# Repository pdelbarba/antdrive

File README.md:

# Antdrive
Magnettic loop antenna driver arduino shield for amateur radio HF

## Notes
Only one limit switch is pinned out as my setup limits torque such that the capacitor cannot be damaged on the other end. If using standard ethernet cable, you have another two lines (one twisted pair) that can be used for additional switches and signaling however.  I may add this at some point but I'm currently focused on other projects.

## Parts

Designed for the Pololu #1208 stepper motor (https://www.pololu.com/product/1208).  While only rated for 10V it has no issues running at >15v for tuning as the Arduino sketch keeps the motor powered off when not rotating to minimize EMI.  The mounting hardware I used is also available from Pololu.

The motor driver module is an A4988 based board also from Pololu (https://www.pololu.com/product/1182).  In theory it should be able to handle much larger stepper motors, 2A per phase and 35V.

Misc drive hardware is as follows:

https://www.amazon.com/gp/product/B07RXJ5GVG/  Drive side pulley

https://www.amazon.com/gp/product/B07W5L6G8L/  Capacitor side pulley

https://www.amazon.com/gp/product/B07KK86NYX/  Note: I've found these belts to be free of metalic strapping which is important for preventing arcing between the capacitor and the motor

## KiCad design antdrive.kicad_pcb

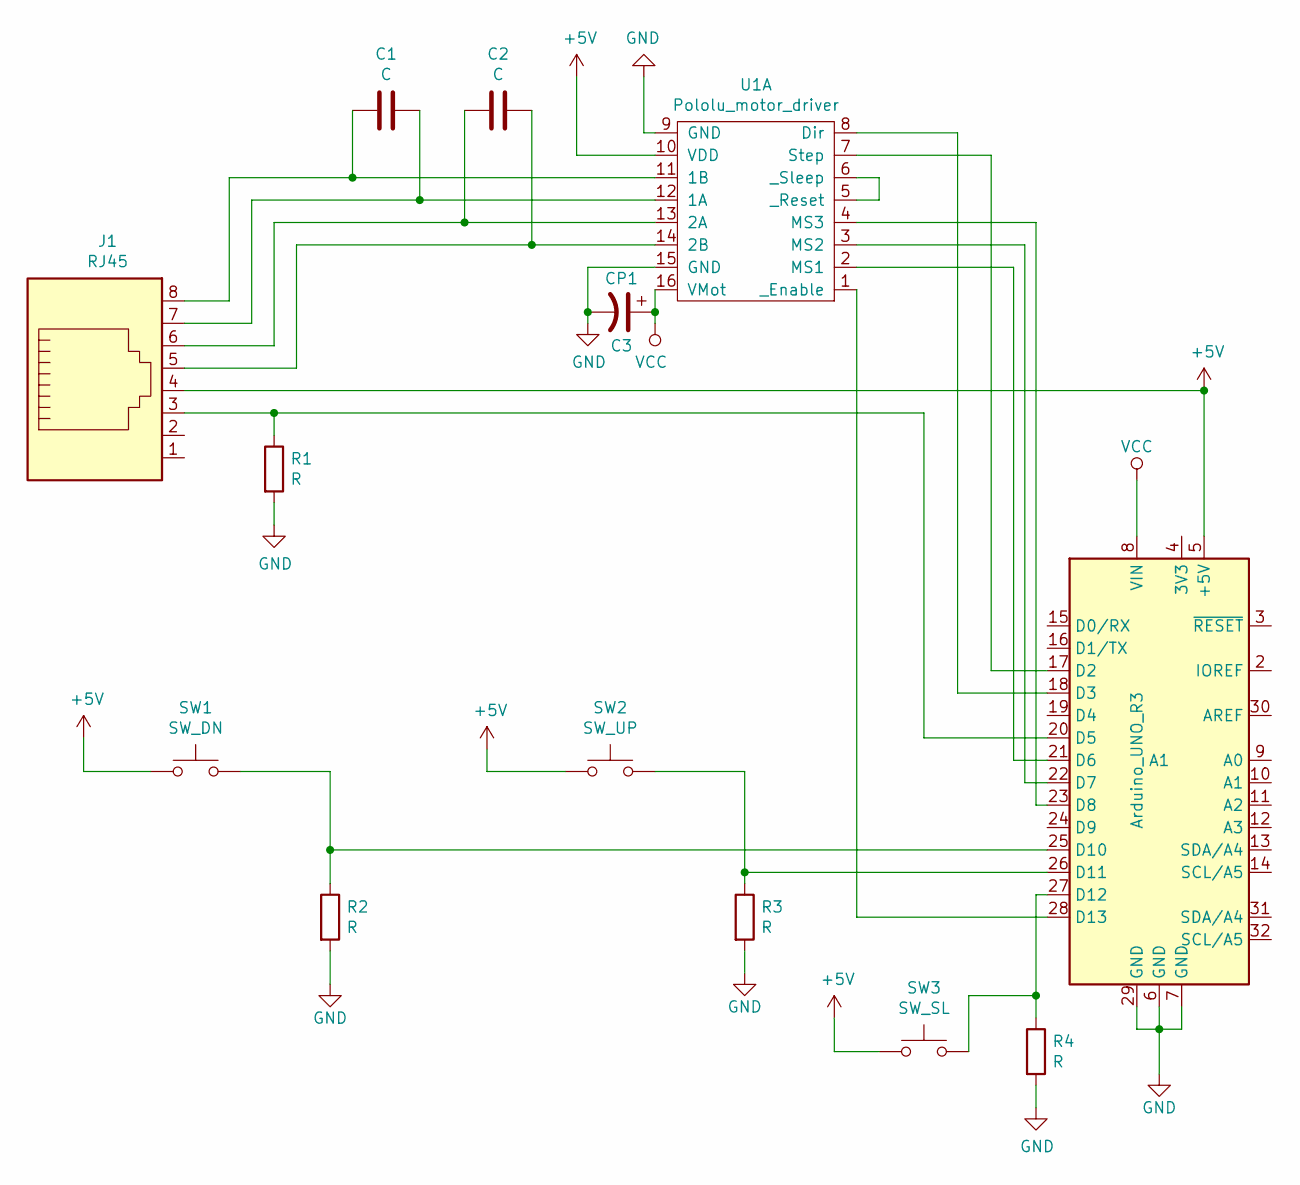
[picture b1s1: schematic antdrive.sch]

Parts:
A1: Arduino_UNO_R3
C1, C2: C; C_Disc_D5.0mm_W2.5mm_P5.00mm
C3: CP1; CP_Radial_D6.3mm_P2.50mm
J1: RJ45; RJ45_Amphenol_54602-x08_Horizontal
R1, R2, R3, R4: R; R_Axial_DIN0207_L6.3mm_D2.5mm_P10.16mm_Horizontal
SW1: SW_DN; SW_PUSH-12mm
SW2: SW_UP; SW_PUSH-12mm
SW3: SW_SL; SW_PUSH-12mm
U1: Pololu_motor_driver; Pololu_Breakout-16_15.2x20.3mm

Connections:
+5V: A1.5 (+5V), J1.4, SW1.1, SW2.1, SW3.1, U1.10 (VDD)
GND: A1.6 (GND), A1.7 (GND), A1.29 (GND), C3.2, R1.2, R2.2, R3.2, R4.2, U1.9 (GND), U1.15 (GND)
unnamed: A1.17 (D2), U1.7 (Step)
unnamed: A1.18 (D3), U1.8 (Dir)
unnamed: A1.20 (D5), J1.3, R1.1
unnamed: A1.21 (D6), U1.2 (MS1)
unnamed: A1.22 (D7), U1.3 (MS2)
unnamed: A1.23 (D8), U1.4 (MS3)
unnamed: A1.25 (D10), R2.1, SW1.2
unnamed: A1.26 (D11), R3.1, SW2.2
unnamed: A1.27 (D12), R4.1, SW3.2
unnamed: A1.28 (D13), U1.1 (_Enable)
unnamed: C1.1, J1.7, U1.12 (1A)
unnamed: C1.2, J1.8, U1.11 (1B)
unnamed: C2.1, J1.5, U1.14 (2B)
unnamed: C2.2, J1.6, U1.13 (2A)
unnamed: U1.5 (_Reset), U1.6 (_Sleep)
VCC: A1.8 (VIN), C3.1, U1.16 (VMot)

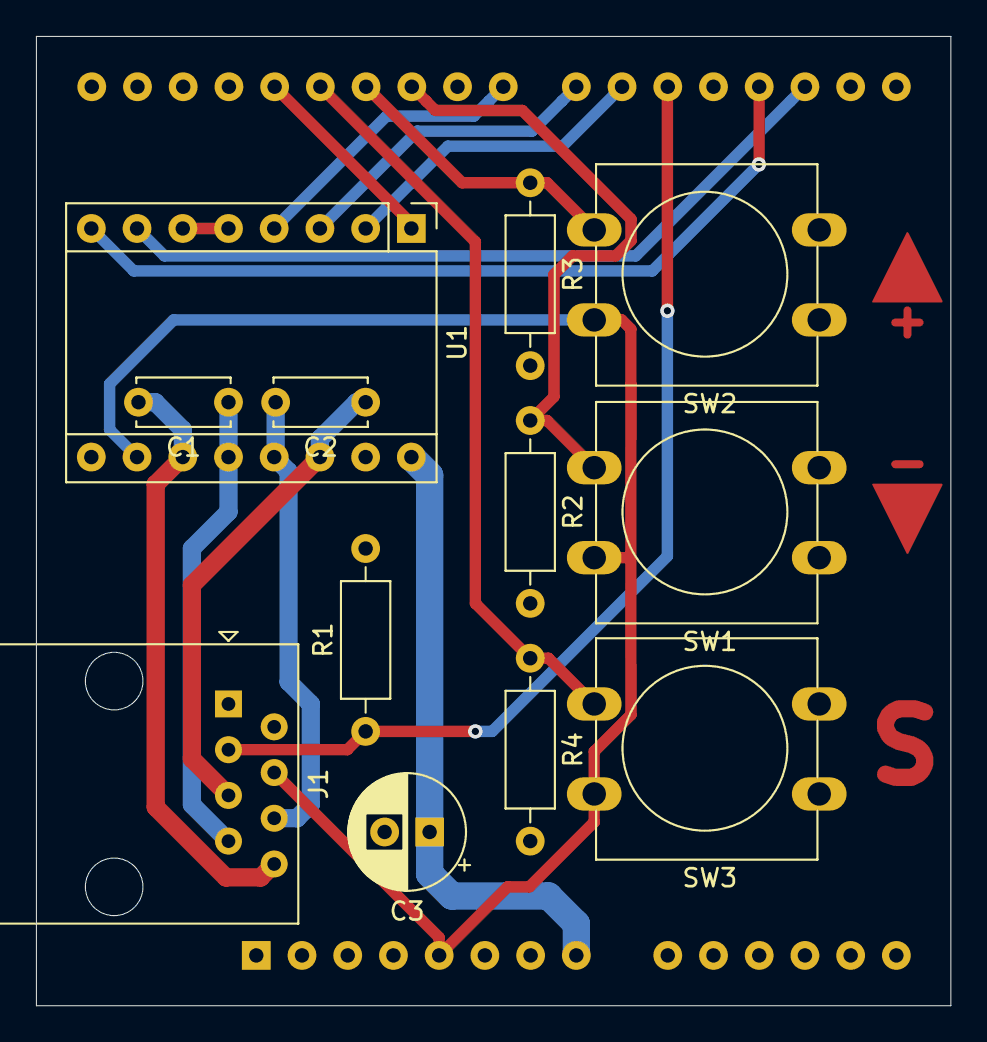
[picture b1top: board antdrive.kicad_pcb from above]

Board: 2 copper layers, 50.8 x 53.8 mm, 13 parts (1 on the bottom side), 18 nets.

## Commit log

2020-02-07 adds project files
2020-03-31 Adds hardware docs to readme, schematic pdf
2020-03-31 Fixes readme formatting
